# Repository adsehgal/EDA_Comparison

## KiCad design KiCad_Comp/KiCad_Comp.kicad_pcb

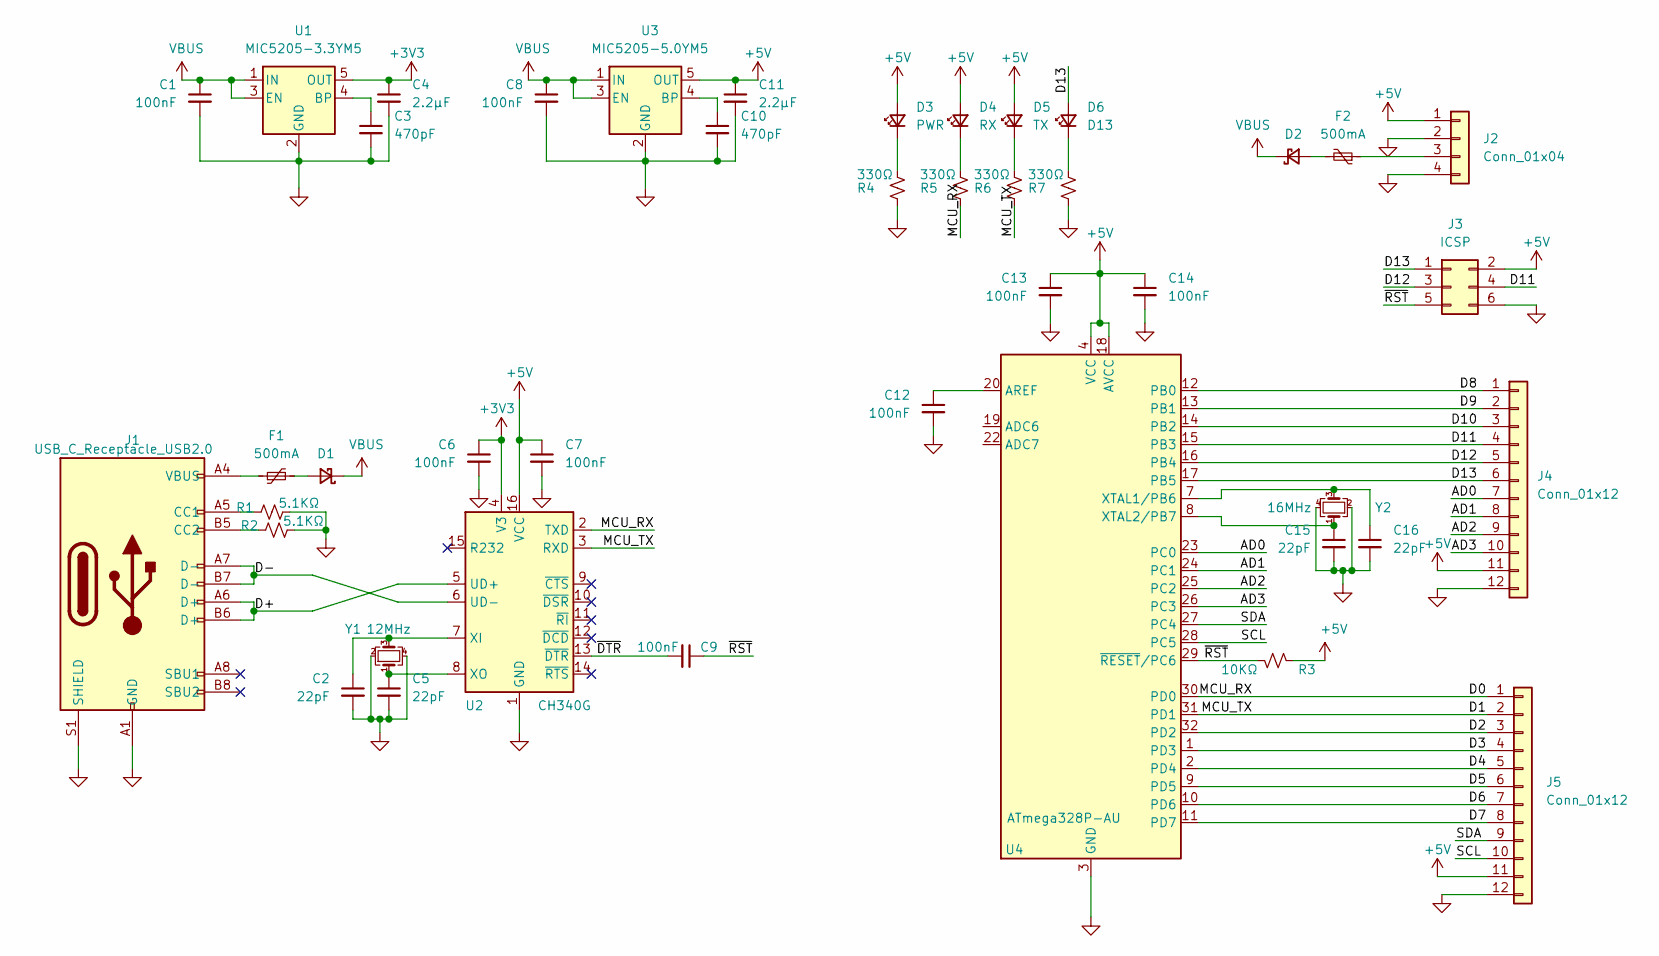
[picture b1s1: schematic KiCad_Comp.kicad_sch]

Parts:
C1, C6, C7, C8, C9, C12, C13, C14: 100nF; C_0805_2012Metric
C2, C5, C15, C16: 22pF; C_0805_2012Metric
C3, C10: 470pF; C_0805_2012Metric
C4, C11: 2.2µF; C_0805_2012Metric
D1, D2: D_Schottky_Small; D_0805_2012Metric
D3: PWR; LED_0805_2012Metric
D4: RX; LED_0805_2012Metric
D5: TX; LED_0805_2012Metric
D6: D13; LED_0805_2012Metric
F1, F2: 500mA; Fuse_0805_2012Metric
J1: USB_C_Receptacle_USB2.0; USB_C_Receptacle_HRO_TYPE-C-31-M-12
J2: Conn_01x04; PinHeader_1x04_P2.54mm_Vertical
J3: ICSP; PinHeader_2x03_P2.54mm_Vertical
J4, J5: Conn_01x12; PinHeader_1x12_P2.54mm_Vertical
R1, R2: 5.1KΩ; R_0805_2012Metric
R3: 10KΩ; R_0805_2012Metric
R4, R5, R6, R7: 330Ω; R_0805_2012Metric
U1: MIC5205-3.3YM5; SOT-23-5
U2: CH340G; SOIC-16_3.9x9.9mm_P1.27mm
U3: MIC5205-5.0YM5; SOT-23-5
U4: ATmega328P-AU; TQFP-32_7x7mm_P0.8mm
Y1: 12MHz; Crystal_SMD_3225-4Pin_3.2x2.5mm
Y2: 16MHz; Crystal_SMD_3225-4Pin_3.2x2.5mm

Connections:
+3V3: C4.1, C6.1, U1.5 (OUT), U2.4 (V3)
+5V: C7.1, C11.1, C13.1, C14.1, D3.2 (A), D4.2 (A), D5.2 (A), J2.1, J3.2, J4.11, J5.11, R3.2, U2.16 (VCC), U3.5 (OUT), U4.4 (VCC), U4.6 (VCC), U4.18 (AVCC)
/AD0: J4.7, U4.23 (PC0)
/AD1: J4.8, U4.24 (PC1)
/AD2: J4.9, U4.25 (PC2)
/AD3: J4.10, U4.26 (PC3)
/D0: J5.1, R5.1, U2.2 (TXD), U4.30 (PD0)
/D1: J5.2, R6.1, U2.3 (RXD), U4.31 (PD1)
/D2: J5.3, U4.32 (PD2)
/D3: J5.4, U4.1 (PD3)
/D4: J5.5, U4.2 (PD4)
/D5: J5.6, U4.9 (PD5)
/D6: J5.7, U4.10 (PD6)
/D7: J5.8, U4.11 (PD7)
/D8: J4.1, U4.12 (PB0)
/D9: J4.2, U4.13 (PB1)
/D10: J4.3, U4.14 (PB2)
/D11: J3.4, J4.4, U4.15 (PB3)
/D12: J3.3, J4.5, U4.16 (PB4)
/D13: D6.2 (A), J3.1, J4.6, U4.17 (PB5)
/D+: J1.A6 (D+), J1.B6 (D+), U2.5 (UD+)
/D-: J1.A7 (D-), J1.B7 (D-), U2.6 (UD-)
/SCL: J5.10, U4.28 (PC5)
/SDA: J5.9, U4.27 (PC4)
/~DTR: C9.2, U2.13 (~DTR)
/~RST: C9.1, J3.5, R3.1, U4.29 (~RESET~/PC6)
GND: C1.2, C2.2, C3.2, C4.2, C5.2, C6.2, C7.2, C8.2, C10.2, C11.2, C12.2, C13.2, C14.2, C15.2, C16.2, J1.A1 (GND), J1.A12 (GND), J1.B1 (GND), J1.B12 (GND), J1.S1 (SHIELD), J2.2, J2.4, J3.6, J4.12, J5.12, R1.2, R2.2, R4.1, R7.1, U1.2 (GND), U2.1 (GND), U3.2 (GND), U4.3 (GND), U4.5 (GND), U4.21 (GND), Y1.2, Y1.4, Y2.2, Y2.4
unnamed: C2.1, U2.7 (XI), Y1.3
unnamed: C3.1, U1.4 (BP)
unnamed: C5.1, U2.8 (XO), Y1.1
unnamed: C10.1, U3.4 (BP)
unnamed: C12.1, U4.20 (AREF)
unnamed: C15.1, U4.8 (XTAL2/PB7), Y2.1
unnamed: C16.1, U4.7 (XTAL1/PB6), Y2.3
unnamed: D1.2 (A), F1.2
unnamed: D2.2 (A), F2.2
unnamed: D3.1 (K), R4.2
unnamed: D4.1 (K), R5.2
unnamed: D5.1 (K), R6.2
unnamed: D6.1 (K), R7.2
unnamed: F1.1, J1.A4 (VBUS), J1.A9 (VBUS), J1.B4 (VBUS), J1.B9 (VBUS)
unnamed: F2.1, J2.3
unnamed: J1.A5 (CC1), R1.1
unnamed: J1.B5 (CC2), R2.1
VBUS: C1.1, C8.1, D1.1 (K), D2.1 (K), U1.1 (IN), U1.3 (EN), U3.1 (IN), U3.3 (EN)

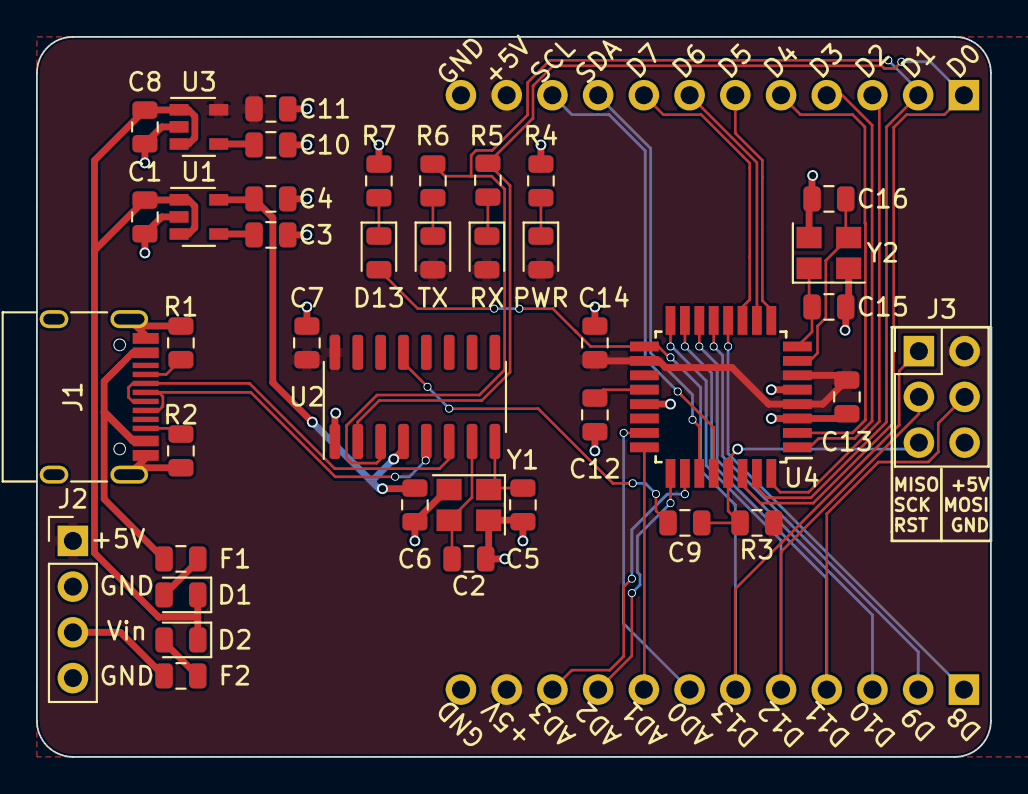
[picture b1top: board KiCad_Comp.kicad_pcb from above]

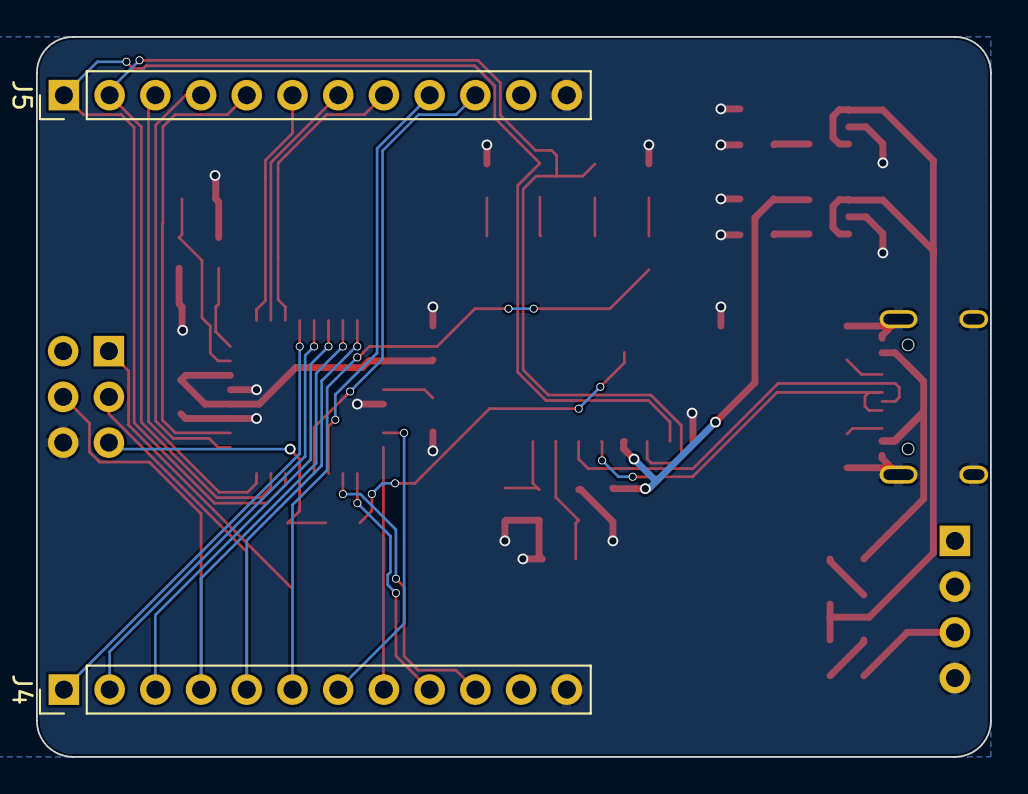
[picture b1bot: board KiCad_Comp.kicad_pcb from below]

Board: 2 copper layers, 53.0 x 40.0 mm, 42 parts (2 on the bottom side), 45 nets.

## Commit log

2020-08-27 KiCad project push
2020-08-27 kicad update
